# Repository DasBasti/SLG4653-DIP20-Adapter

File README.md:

# SLG4653-DIP20-Adapter

Adapter for mounting GreenPAK5 (SLG4653X) to DIP 20

Since Silego now sells DIP-20 boards for fast prototyping (http://www.silego.com/buy/index.php?main_page=product_info&cPath=61&products_id=508) there is no longer a need for those boards.

## SLG4653X PCB ##
Project Sil contains a DIP-20 sized PCB with a mounting place for SLG4653X and a 0603 capacitor.

## DIP-20 Programming adapter ##
Project Sil_Adapter contains a PCB to mount the DIP-20 to the Silego Programming board.

More information: http://www.kurzschluss-blog.de/2016/09/greenpak5-im-dil-20-pinout-adapterboard.html

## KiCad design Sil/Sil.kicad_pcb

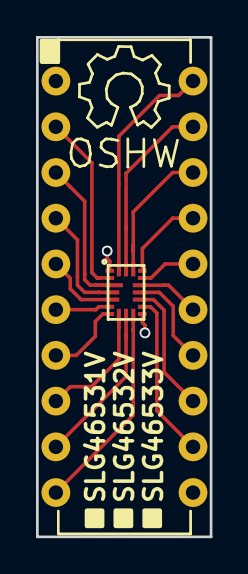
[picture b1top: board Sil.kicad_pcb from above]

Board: 2 copper layers, 9.7 x 27.7 mm, 3 parts (1 on the bottom side), 20 nets.

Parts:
C1: 100n; C_0402
P1: CONN_01X20; DIP-20_W7.62mm
U1: SLG46531; SLG4653X

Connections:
GND: C1.1, P1.11, U1.11
unnamed: C1.2, P1.1, U1.1
unnamed: P1.2, U1.2
unnamed: P1.3, U1.3
unnamed: P1.4, U1.4
unnamed: P1.5, U1.5
unnamed: P1.6, U1.6
unnamed: P1.7, U1.7
unnamed: P1.8, U1.8
unnamed: P1.9, U1.9
unnamed: P1.10, U1.10
unnamed: P1.12, U1.12
unnamed: P1.13, U1.13
unnamed: P1.14, U1.14
unnamed: P1.15, U1.15
unnamed: P1.16, U1.16
unnamed: P1.17, U1.17
unnamed: P1.18, U1.18
unnamed: P1.19, U1.19
unnamed: P1.20, U1.20

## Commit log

2016-09-29 initial commit of files sent off for production
2016-09-29 added picture for README.md
